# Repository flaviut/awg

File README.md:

# Arbitrary Waveform Generator

**DOES NOT WORK**, see issues

## Goals

- 0-15MHz
- drive a 50-ohm load
- ±3.3V output voltage

## Credits

Rebuilt from the ground up, but originally derived from the following:

- https://www.instructables.com/Arbitrary-Wave-Generator-With-the-Raspberry-Pi-Pic/
- https://www.instructables.com/Poor-Mans-Waveform-Generator-Based-on-RP2040-Raspb/
- https://github.com/F6ITU/AWG

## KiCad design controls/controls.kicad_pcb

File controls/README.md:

The optional controls board for this device

Broken out into a separate board in order to reduce JLCPCB cost, as well as
because it can probably be done by hand-soldering to panel-mounted components.

Designed to be placed on the left side of the LCD display, and clipped into a
3d-printed enclosure.

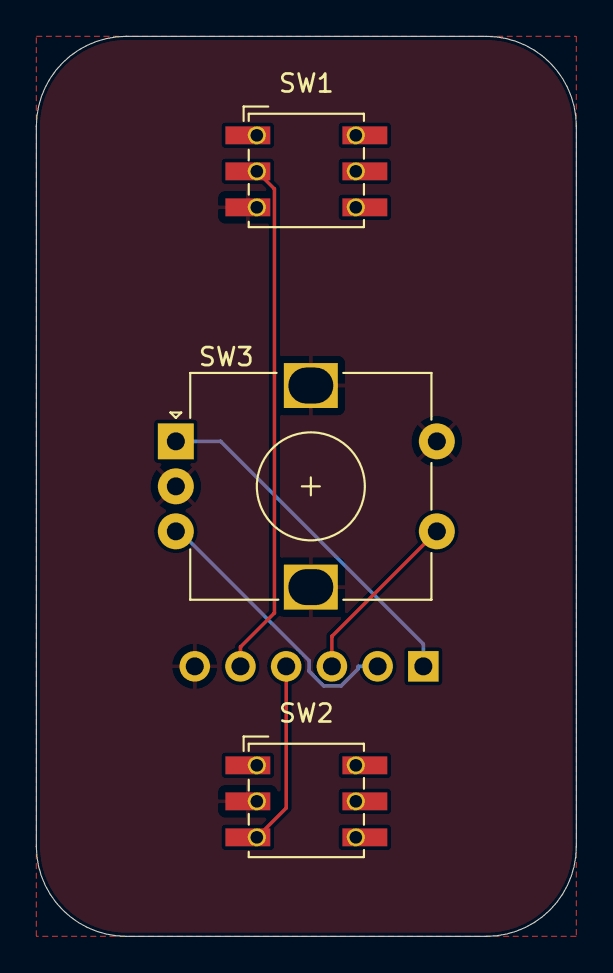
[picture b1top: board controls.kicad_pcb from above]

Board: 2 copper layers, 30.0 x 50.0 mm, 4 parts (1 on the bottom side), 6 nets.

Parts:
J9: Controls; PinSocket_1x06_P2.54mm_Vertical
SW1: Prev; Square_PB
SW2: Next; Square_PB
SW3: Encoder; RotaryEncoder_Alps_EC12E-Switch_Vertical_H20mm

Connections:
/B_NE: J9.4, SW2.3 (C)
/B_PR: J9.5, SW1.2 (B)
/ENC_A: J9.1, SW3.A
/ENC_B: J9.2, SW3.B
/ENC_SW: J9.3, SW3.S2
GND: J9.6, SW1.3 (C), SW2.2 (B), SW3.C, SW3.MP, SW3.S1

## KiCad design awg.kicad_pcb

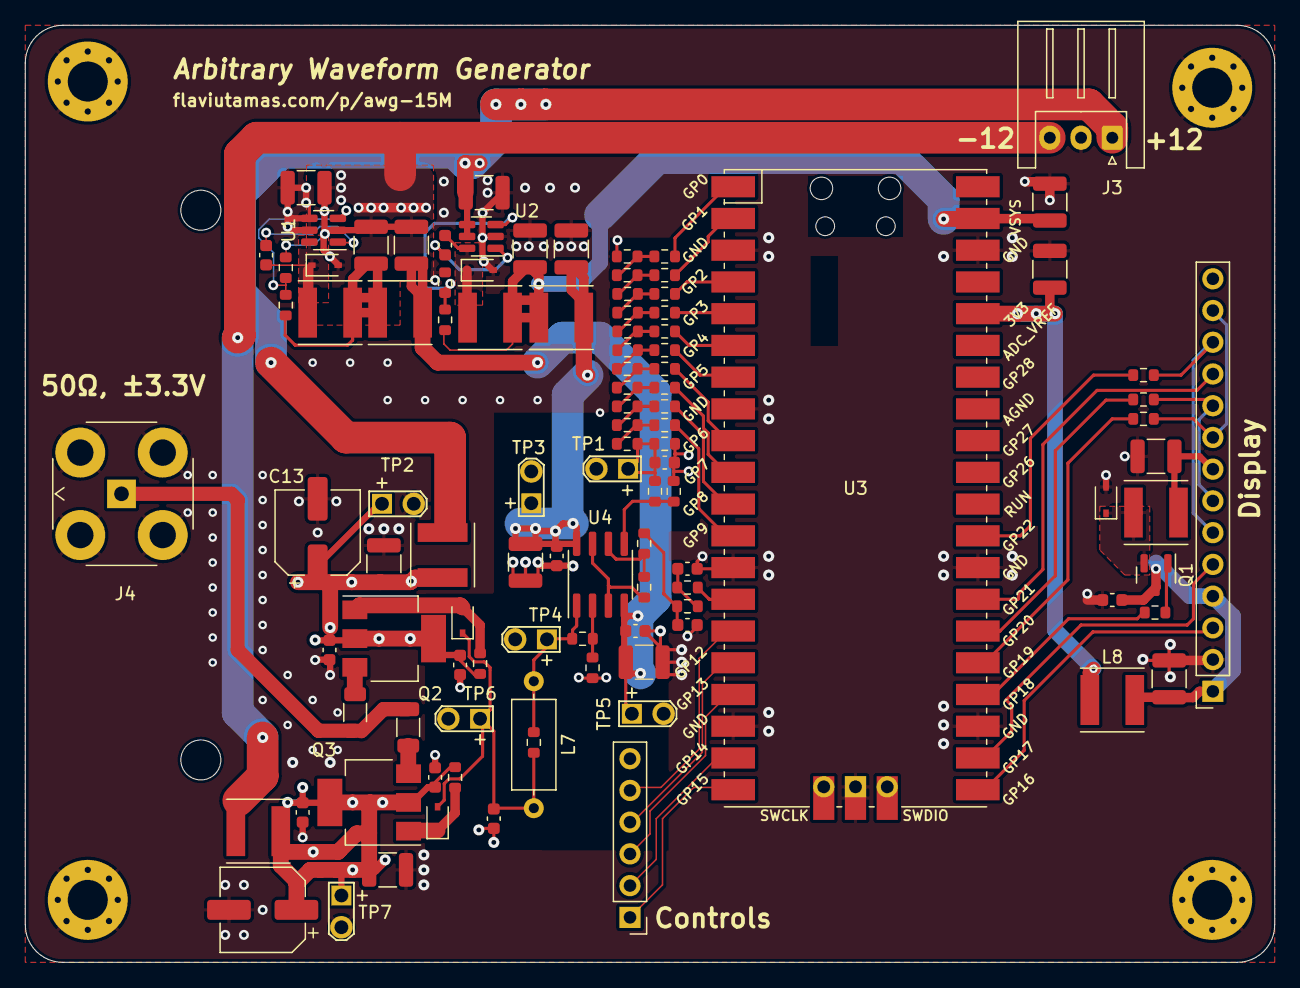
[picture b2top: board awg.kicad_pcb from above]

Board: 4 copper layers, 100.0 x 75.0 mm, 110 parts (0 on the bottom side), 70 nets.

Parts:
C1, C2, C3, C4, C5, C7, C8, C10, C11, C15, C16, C22, C24, C28: 22u; C_1210_3225Metric
C6, C9, C14, C17, C18, C19, C20, C21, C23, C25, C26: 100n; C_0603_1608Metric
C12, C27: DNP; C_0603_1608Metric
C13, C29: 100u; CP_Elec_6.3x5.4_Nichicon
D1, D2, D3: 1N5819WS; D_SOD-323
D4, D5: 1N4148WS; D_SOD-323
H1, H2: MountingHole; MountingHole_3.2mm_M3
J1, J2, J6, J7: Conn_01x01; MountingHole_3.2mm_M3_Pad_Via
J3: Conn_01x03; JST_XH_S3B-XH-A_1x03_P2.50mm_Horizontal
J4: BNC; BNC_DOSIN_801_0050_Horizontal
J5: Conn_01x14; PinSocket_1x14_P2.54mm_Vertical
J8: Controls; PinHeader_1x06_P2.54mm_Vertical
L1, L2, L3, L4, L5, L6, L8, L9: 47u; L_Taiyo-Yuden_NR-50xx
L7: 51n; L_Axial_L7.0mm_D3.3mm_P10.16mm_Horizontal_Fastron_MICC
Q1: S9015; SOT-23
Q2: FZT653; SOT-223-3_TabPin2
Q3: FZT753; SOT-223-3_TabPin2
R1, R2, R5, R8, R11, R14, R16, R18, R21, R24, R27, R36: 2k; R_0603_1608Metric
R3, R12, R34, R35: 68k; R_0603_1608Metric
R4, R7, R10, R13, R15, R17, R20, R23, R26, R30, R31, R32, R33, R37, R38, R39, R43: 1k; R_0603_1608Metric
R6, R9: 12k; R_0603_1608Metric
R19, R22, R25: 27; R_0603_1608Metric
R28: 0; R_0603_1608Metric
R29: DNP; R_0603_1608Metric
R40, R41: 1; R_1206_3216Metric
R42: 10; R_0603_1608Metric
TP1, TP2, TP3, TP4, TP5, TP6, TP7: TestPoint_2Pole; TestPoint_2Pads_Pitch2.54mm_Drill1mm
U1, U2: BD9G101G; SOT-23-6
U3: Pico; RPi_Pico_SMD
U4: LMH6658; SOIC-8_3.9x4.9mm_P1.27mm

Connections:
+3V3: C10.2, L8.1, U3.36 (3V3)
+5V: C8.2, C14.2, C15.2, L4.2, TP3.1, U4.8 (V+)
+5VD: C3.2, C7.2, L3.2, L4.1, R12.2, U3.39 (VSYS)
+12V: C13.1, C16.2, C21.2, C23.2, L6.2, Q2.2 (C), R38.1, TP2.1
-5V: C5.2, C20.1, C22.1, L2.2, TP5.1, U4.4 (V-)
-12V: C25.1, C26.1, C28.2, C29.1, L9.2, Q3.2 (C), R43.2, TP7.1
/B_NE: J8.4, U3.16 (GPIO12)
/B_PR: J8.5, U3.15 (GPIO11)
/DAT/CMD: J5.5, U3.22 (GPIO17)
/DC_PWM: R34.2, U3.14 (GPIO10)
/ENC_A: J8.1, U3.20 (GPIO15)
/ENC_B: J8.2, U3.19 (GPIO14)
/ENC_SW: J8.3, U3.17 (GPIO13)
/LCD_3V3: C18.2, C24.2, J5.1, J5.4, L8.2, Q1.3 (C)
/LCD_CS: J5.3, U3.21 (GPIO16)
/LCD_LED: C11.2, J5.8, L5.2
/LCD_PWM: R36.1, U3.24 (GPIO18)
/MISO: J5.9, J5.13, R25.1
/MOSI: J5.6, J5.12, R19.1
/SCLK: J5.7, J5.10, R22.1
/TCH_CS: J5.11, U3.27 (GPIO21)
/amp/DAC_OUT: R26.1, R27.2, R28.1
/amp/GH: D4.2 (A), Q2.1 (B), R38.2
/amp/GL: D5.1 (K), Q3.1 (B), R43.1
/amp/OUT: J4.1 (In), R40.2, R41.1
/power/+12V_UNFIL: C2.2, J3.1, L6.1, U2.4 (EN), U2.5 (VIN)
/power/-12V_UNFIL: C1.1, C4.1, C5.1, D1.2 (A), J3.3, L9.1, R3.1, U1.2 (GND)
GND: C1.2, C2.1, C3.1, C7.1, C8.1, C10.1, C11.1, C12.2, C13.2, C14.1, C15.1, C16.1, C17.1, C18.1, C19.1, C20.2, C21.1, C22.2, C23.1, C24.1, C25.2, C26.2, C27.1, C28.1, C29.2, D2.2 (A), D3.2 (A), J1.1, J2.1, J3.2, J4.2 (Ext), J5.2, J6.1, J7.1, J8.6, R1.2, R6.1, R29.2, R31.1, R39.2, TP1.2, TP2.2, TP3.2, TP4.2, TP5.2, TP6.2, TP7.2, U1.4 (EN), U1.5 (VIN), U2.2 (GND), U3.3 (GND), U3.8 (GND), U3.13 (GND), U3.18 (GND), U3.23 (GND), U3.28 (GND), U3.38 (GND), U3.42 (GND)
unnamed: C9.1, D1.1 (K), L1.1, U1.6 (LX)
unnamed: C9.2, U1.1 (BST)
unnamed: C6.1, D2.1 (K), L3.1, U2.6 (LX)
unnamed: C6.2, U2.1 (BST)
unnamed: C4.2, L1.2, L2.1, R9.2
unnamed: C27.2, D4.1 (K), D5.2 (A), L7.2, R42.2, TP6.1
unnamed: C12.1, R28.2, R29.1, R30.1, TP1.1
unnamed: C17.2, R34.1, R35.2
unnamed: C19.2, R32.1, R35.1
unnamed: D3.1 (K), L5.1, Q1.2 (E)
unnamed: L7.1, R37.2, R42.1, TP4.1, U4.1
unnamed: Q2.3 (E), R40.1
unnamed: Q1.1 (B), R36.2
unnamed: Q3.3 (E), R41.2
unnamed: R1.1, R2.2, R4.2
unnamed: R2.1, U3.1 (GPIO0)
unnamed: R4.1, R5.2, R7.2
unnamed: R5.1, U3.2 (GPIO1)
unnamed: R3.2, R9.1, U1.3 (FB)
unnamed: R6.2, R12.1, U2.3 (FB)
unnamed: R8.1, U3.4 (GPIO2)
unnamed: R7.1, R8.2, R10.2
unnamed: R10.1, R11.2, R13.2
unnamed: R11.1, U3.5 (GPIO3)
unnamed: R13.1, R14.2, R15.2
unnamed: R14.1, U3.6 (GPIO4)
unnamed: R15.1, R16.2, R17.2
unnamed: R16.1, U3.7 (GPIO5)
unnamed: R19.2, U3.29 (GPIO22)
unnamed: R22.2, U3.26 (GPIO20)
unnamed: R25.2, U3.25 (GPIO19)
unnamed: R17.1, R18.2, R20.2
unnamed: R18.1, U3.9 (GPIO6)
unnamed: R20.1, R21.2, R23.2
unnamed: R21.1, U3.10 (GPIO7)
unnamed: R23.1, R24.2, R26.2
unnamed: R24.1, U3.11 (GPIO8)
unnamed: R27.1, U3.12 (GPIO9)
unnamed: R37.1, R39.1, U4.2 (-)
unnamed: R30.2, R31.2, U4.5 (+)
unnamed: R33.1, U4.3 (+), U4.7
unnamed: R32.2, R33.2, U4.6 (-)

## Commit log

2022-11-14 Update gitignore
2022-11-14 Rename power supply schematic
2022-11-20 Redesign
2022-11-20 Add kibot
2022-11-20 Make design more compact
    Fitting it on a 100x70mm PCB means it's far cheaper to produce
2022-11-21 consistant fonts
2022-11-21 Add optional controls board
2022-11-21 Fix JLCPCB missing inner layers
